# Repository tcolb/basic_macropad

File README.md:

# basic_macropad
 
A small macropad with programmable keys, hot-swap MX connectors, LEDS, 3D printed case, and volume encoder

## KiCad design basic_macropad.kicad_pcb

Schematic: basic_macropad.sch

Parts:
C1, C2, C3: 0.1uF; C_0805_2012Metric
C4: 10uF; C_0805_2012Metric
C5, C6: 22pF; C_0805_2012Metric
C7: 1uF; C_0805_2012Metric
D1, D2, D3, D4, D5, D6: SOD-123; D_SOD-123
D7, D8: WS2812B; LED_WS2812B_PLCC4_5.0x5.0mm_P3.2mm
F1: 500mA; Fuse_1206_3216Metric
H1, H2, H3, H4: MountingHole; MountingHole_2.2mm_M2
MX1, MX2, MX3, MX4, MX5: MX-NoLED; MXOnly-1U-Hotswap
R1, R4: 10k; R_0805_2012Metric
R2, R3: 5.1k; R_0805_2012Metric
R5, R6: 22; R_0805_2012Metric
R7: 500; R_0805_2012Metric
SW1: SW_Push; SKQG-1155865
SW2: Rotary_Encoder_Switch; RotaryEncoder_Alps_EC11E-Switch_Vertical_H20mm_CircularMoun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
U1: ATmega32U4-AU; TQFP-44_10x10mm_P0.8mm
U2: PRTR5V0U2X; SOT143B
USB1: HRO-TYPE-C-31-M-12; HRO-TYPE-C-31-M-12-Assembly
Y1: 16MHz; Crystal_SMD_3225-4Pin_3.2x2.5mm

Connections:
+5V: C1.1, C2.1, C3.1, C4.1, D7.1 (VDD), D8.1 (VDD), F1.1, R4.1, U1.2 (UVCC), U1.7 (VBUS), U1.14 (VCC), U1.24 (AVCC), U1.34 (VCC), U1.44 (AVCC)
COL0: MX1.1 (COL), MX3.1 (COL), U1.27 (PD7)
COL1: MX2.1 (COL), MX4.1 (COL), U1.29 (PB5)
COL2: MX5.1 (COL), SW2.S2, U1.30 (PB6)
D+: R6.2, U1.4 (D+)
D-: R5.2, U1.3 (D-)
ENC_A: SW2.A, U1.31 (PC6)
ENC_B: SW2.B, U1.32 (PC7)
GND: C1.2, C2.2, C3.2, C4.2, C5.2, C6.2, C7.2, D7.3 (VSS), D8.3 (VSS), R1.1, R2.2, R3.2, SW1.1, SW2.C, U1.5 (UGND), U1.15 (GND), U1.23 (GND), U1.35 (GND), U1.43 (GND), U2.1 (GND), USB1.1 (GND), USB1.12 (GND), USB1.13 (SHIELD), Y1.2, Y1.4
unnamed: C5.1, U1.17 (XTAL1), Y1.1
unnamed: C6.1, U1.16 (XTAL2), Y1.3
unnamed: C7.1, U1.6 (UCAP)
unnamed: D1.2 (A), MX1.2 (ROW)
unnamed: D2.2 (A), MX2.2 (ROW)
unnamed: D3.2 (A), MX3.2 (ROW)
unnamed: D4.2 (A), MX4.2 (ROW)
unnamed: D5.2 (A), MX5.2 (ROW)
unnamed: D6.2 (A), SW2.S1
unnamed: D7.2 (DOUT), D8.4 (DIN)
unnamed: R1.2, U1.33 (~HWB~/PE2)
unnamed: R2.1, USB1.10 (CC2)
unnamed: R3.1, USB1.4 (CC1)
unnamed: R4.2, SW1.2, U1.13 (~RESET)
unnamed: R5.1, U2.3 (IO2), USB1.5 (DN2), USB1.7 (DN1)
unnamed: R6.1, U2.2 (IO1), USB1.6 (DP1), USB1.8 (DP2)
RGBLED: D7.4 (DIN), R7.1, R7.2, U1.25 (PD4)
ROW0: D1.1 (K), D2.1 (K), D6.1 (K), U1.26 (PD6)
ROW1: D3.1 (K), D4.1 (K), D5.1 (K), U1.28 (PB4)
VCC: F1.2, U2.4 (VCC), USB1.2 (VBUS), USB1.11 (VBUS)

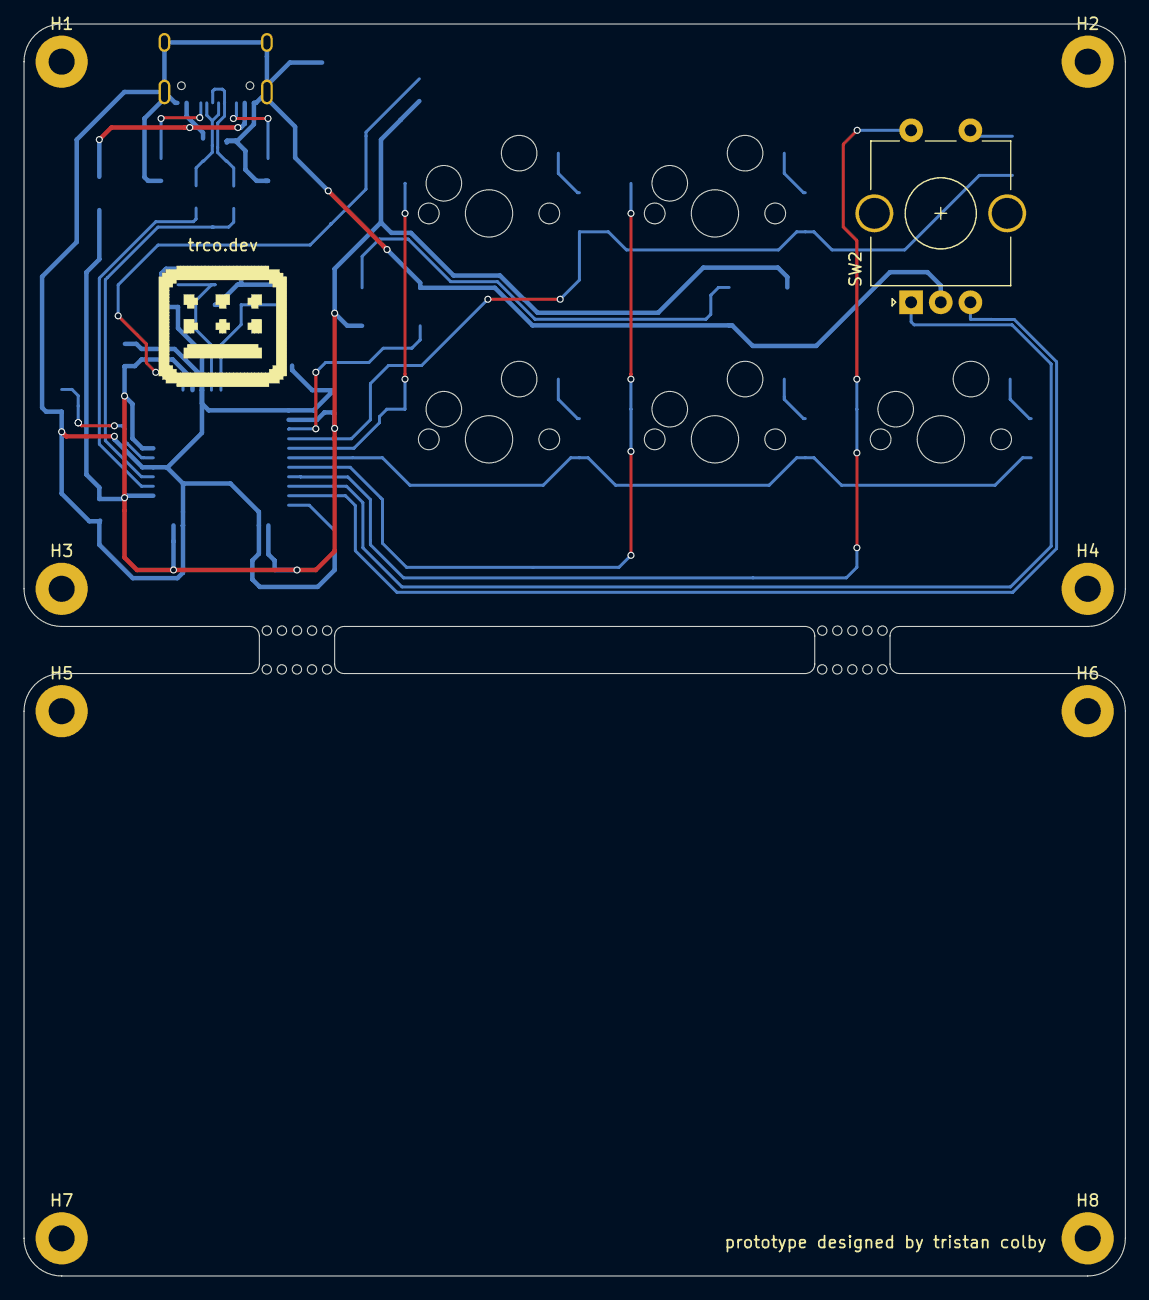
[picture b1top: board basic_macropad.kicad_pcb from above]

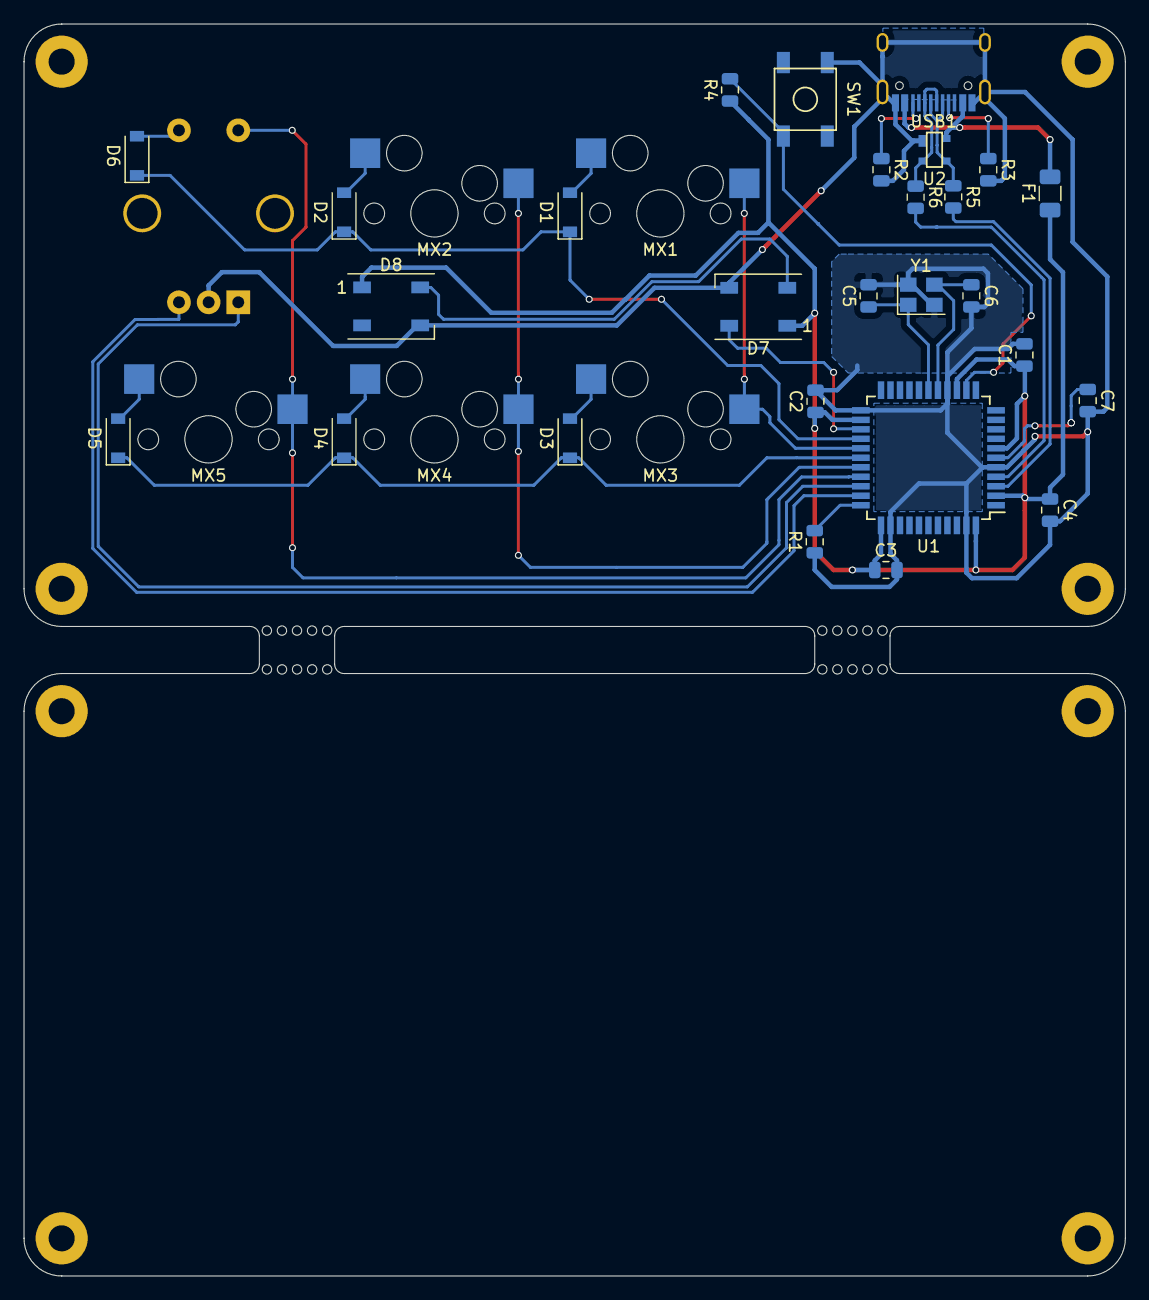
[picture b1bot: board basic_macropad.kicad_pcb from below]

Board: 2 copper layers, 92.9 x 105.6 mm, 42 parts (27 on the bottom side), 29 nets.

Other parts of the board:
H5, H6, H7, H8: MountingHole_Pad; MountingHole_2.2mm_M2_Pad
LOGO: LOGO_Smallest

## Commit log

2020-07-27 Adding kicad project
2020-07-27 Add submodules
2020-07-27 Added footprint libraries
2020-07-27 First try
2020-07-30 Almost done
2020-09-01 Final
2020-09-01 Added images
2020-09-01 Added QMK firmware
